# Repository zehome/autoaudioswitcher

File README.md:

autoaudioswitcher
=================

Introduction
------------
With vintage amplifiers, you have limited input switching capabilities. And they are all manual.
This projects aims to solve this problem.

I have an old kenwood KA-4002 (http://www.hifivintage.eu/product.php?id_product=476) which I love.

So, my solution to this problem, automatic audio input switcher.
Basically, the system will detect which audio input has a signal, and switch to it using a solid state MUX.

The project is in early state. Prototype circuit works on a breadbord. First test PCB done and sent to the factory.

Theory of operation
-------------------
Stereo input is muxed using 10k resistors and AC coupled into an amplifier (saturated).
Then, the signal is compared to a reference voltage using a comparator which charges a CAP.
A MCU will then poll the charge of the CAP and trigger the MUX (ADG409) to switch on the output if needed. (Programmed in the MCU)

Status
------
Early design stage.

Breadboard prototype working.

Testing PCB done and sent to the factory. Gerbers available in GERBERS_REV0/.

Tools
-----
KiCAD 20140622 + bzr4027 (r4027)

Hackaday.io entry
-----------------
http://hackaday.io/project/2282-automatic-audio-input-switcher

OSHW: Automatic audio input switcher based on audio activity

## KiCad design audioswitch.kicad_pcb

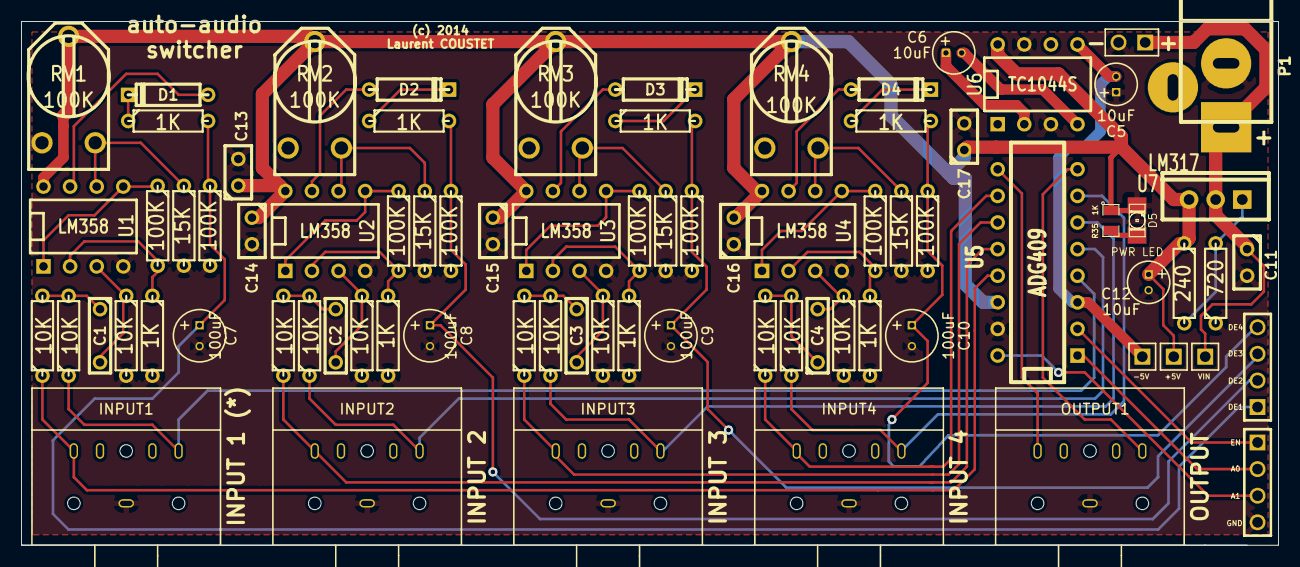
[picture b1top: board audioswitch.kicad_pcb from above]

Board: 2 copper layers, 120.0 x 50.0 mm, 80 parts (0 on the bottom side), 53 nets.

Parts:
C1, C2, C3, C4: 10nF; C2
C5, C6, C12: 10uF; C1.5V4
C7, C8, C9, C10: 100uF; C1V5
C11: 0.1uF; C1
C13, C14, C15, C16, C17: 10nF; C1
D1, D2, D3, D4: DIODE; D3
D5: PWR LED; LED-1206
JACK1: INPUT1; 3.5MMJACK
JACK2: INPUT2; 3.5MMJACK
JACK3: INPUT3; 3.5MMJACK
JACK4: INPUT4; 3.5MMJACK
JACKOUT1: OUTPUT1; 3.5MMJACK
P1: POWER; JACK_ALIM
P2: TESTPWR; PIN_ARRAY_2X1
P3: DETECT CONN; PIN_ARRAY_4x1
P5: CTRL CONN; PIN_ARRAY_4x1
R1, R2, R3, R7, R10, R11, R12, R13, R14, R15, R16, R17: 10K; R3
R4, R9, R18, R19, R20, R27, R28, R29: 1K; R3
R5, R8, R21, R22, R23, R30, R31, R32: 100K; R3
R6, R24, R25, R26: 15K; R3
R33: 720; R3
R34: 240; R3
R35: 1K; SM0805
RV1, RV2, RV3, RV4: 100K; RV2X4
TP1: TP -5V; PIN_ARRAY_1
TP2: TP_VIN; PIN_ARRAY_1
TP3: TP_VCC; PIN_ARRAY_1
U1, U2, U3, U4: LM358; DIP-8__300
U5: ADG409; DIP-16__300
U6: TC1044S; DIP-8__300
U7: LM317; TO220_VERT

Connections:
/-5V: C5.2, TP1.1, U5.3, U6.5
/A0: P5.2, U5.1
/A1: P5.3, U5.16
/CH1LEFT: JACK1.5, R1.1, U5.13
/CH1RIGHT: JACK1.4, R2.1, U5.4
/CH2LEFT: JACK2.5, R7.1, U5.12
/CH2RIGHT: JACK2.4, R10.1, U5.5
/CH3LEFT: JACK3.5, R11.1, U5.11
/CH3RIGHT: JACK3.4, R12.1, U5.6
/CH4LEFT: JACK4.5, R13.1, U5.10
/CH4RIGHT: JACK4.4, R14.1, U5.7
/EN: P5.1, U5.2
/VIN: C11.1, P1.1, P2.1, TP2.1, U7.3
AUDIO1_DETECT: C7.1, P3.1, R8.1, R9.2
AUDIO2_DETECT: C8.1, P3.2, R27.2, R30.1
AUDIO3_DETECT: C9.1, P3.3, R28.2, R31.1
AUDIO4_DETECT: C10.1, P3.4, R29.2, R32.1
GND: C5.1, C7.2, C8.2, C9.2, C10.2, C11.2, C12.2, C13.2, C14.2, C15.2, C16.1, C17.2, D5.2, JACK1.1, JACK2.1, JACK3.1, JACK4.1, JACKOUT1.1, P1.2, P2.2, P5.4, R3.2, R4.2, R6.2, R8.2, R15.2, R16.2, R17.2, R18.2, R19.2, R20.2, R24.2, R25.2, R26.2, R30.2, R31.2, R32.2, R33.1, U1.4, U2.4, U3.4, U4.4, U5.15, U6.3, U6.7
unnamed: R6.1, RV1.3, U1.6
unnamed: R24.1, RV2.3, U2.6
unnamed: R25.1, RV3.3, U3.6
unnamed: R26.1, RV4.3, U4.6
unnamed: C4.2, R17.1, U4.3
unnamed: R23.1, U4.1, U4.5
unnamed: C4.1, R13.2, R14.2
unnamed: R20.1, R23.2, U4.2
unnamed: D4.2, R29.1
unnamed: D4.1, U4.7
unnamed: JACKOUT1.5, U5.9
unnamed: R33.2, R34.2, U7.1
unnamed: C6.2, U6.4
unnamed: R5.1, U1.1, U1.5
unnamed: C1.1, R1.2, R2.2
unnamed: JACKOUT1.4, U5.8
unnamed: D1.2, R9.1
unnamed: D1.1, U1.7
unnamed: C1.2, R3.1, U1.3
unnamed: D5.1, R35.2
unnamed: R22.1, U3.1, U3.5
unnamed: C3.1, R11.2, R12.2
unnamed: R18.1, R21.2, U2.2
unnamed: R19.1, R22.2, U3.2
unnamed: D3.2, R28.1
unnamed: D3.1, U3.7
unnamed: C3.2, R16.1, U3.3
unnamed: C2.1, R7.2, R10.2
unnamed: C6.1, U6.2
unnamed: R4.1, R5.2, U1.2
unnamed: D2.2, R27.1
unnamed: D2.1, U2.7
unnamed: C2.2, R15.1, U2.3
unnamed: R21.1, U2.1, U2.5
VCC: C12.1, C13.1, C14.1, C15.1, C16.2, C17.1, R34.1, R35.1, RV1.2, RV2.2, RV3.2, RV4.2, TP3.1, U1.8, U2.8, U3.8, U4.8, U5.14, U6.8, U7.2

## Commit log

2014-08-05 3D rendered images output of kicad
2014-08-05 Test image on README
2014-08-05 Kenwood amplifier image

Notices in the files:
audioswitch.kicad_pcb:
(c) 2014
